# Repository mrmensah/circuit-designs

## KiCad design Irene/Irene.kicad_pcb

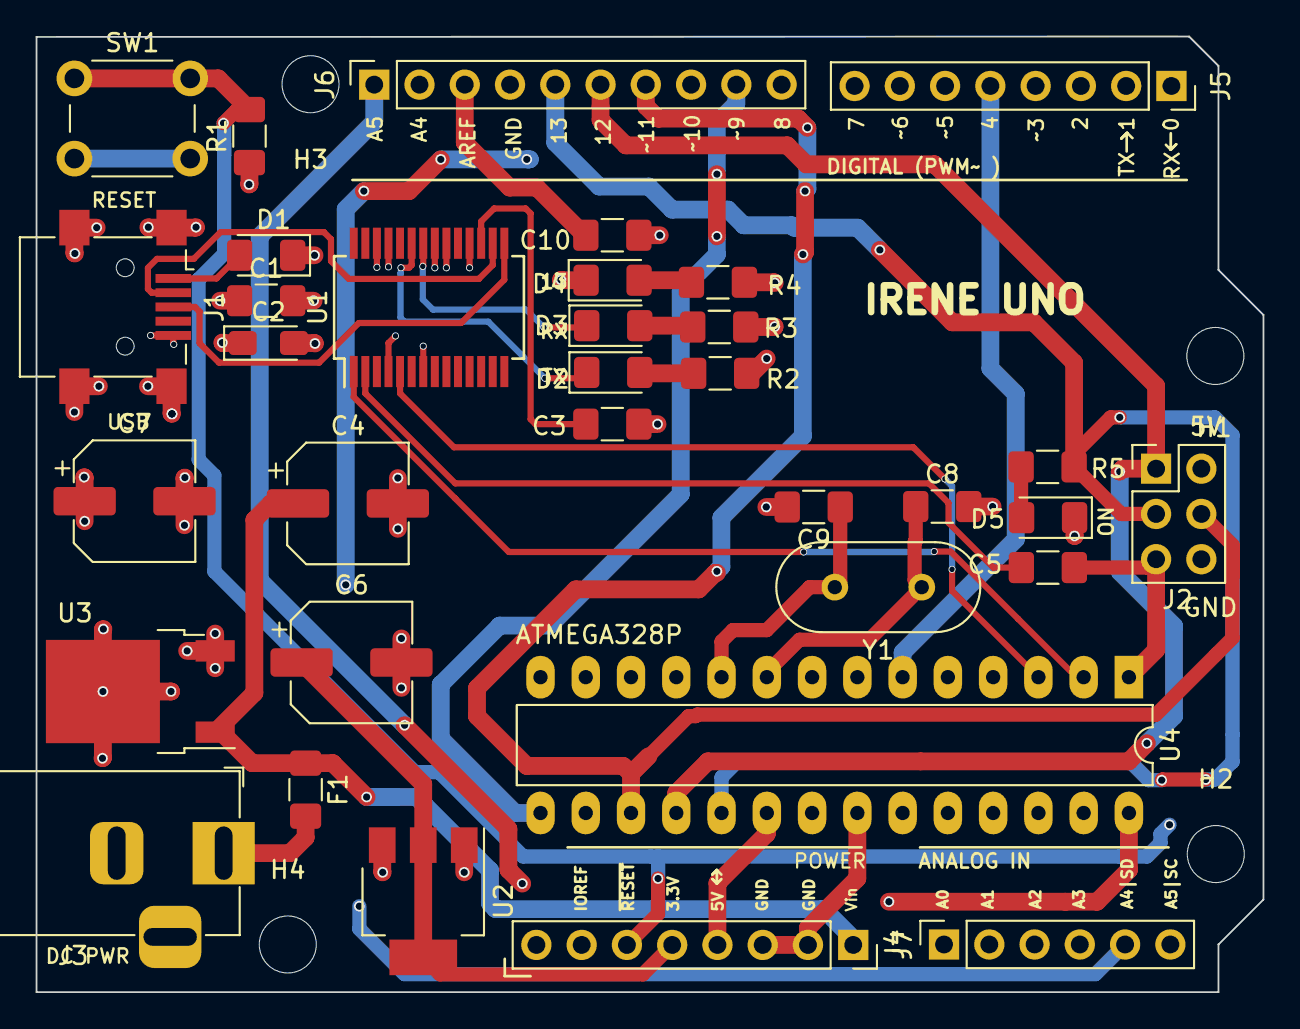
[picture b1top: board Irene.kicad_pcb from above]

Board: 4 copper layers, 68.8 x 53.6 mm, 38 parts (0 on the bottom side), 40 nets.

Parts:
C1, C3, C5, C10: 100nF; C_1206_3216Metric_Pad1.42x1.75mm_HandSolder
C2: 4.7uF; CP_EIA-3216-10_Kemet-I_Pad1.58x1.35mm_HandSolder
C4: 480uF; CP_Elec_6.3x5.4
C6, C7: 100uF; CP_Elec_6.3x5.4
C8, C9: 22pF; C_1206_3216Metric_Pad1.42x1.75mm_HandSolder
D1: D_Schottky; D_1206_3216Metric_Pad1.42x1.75mm_HandSolder
D2: TX LED; LED_1206_3216Metric_Pad1.42x1.75mm_HandSolder
D3: RX LED; LED_1206_3216Metric_Pad1.42x1.75mm_HandSolder
D4: RED; LED_1206_3216Metric_Pad1.42x1.75mm_HandSolder
D5: LED; LED_1206_3216Metric_Pad1.42x1.75mm_HandSolder
F1: 1A; Fuse_1206_3216Metric_Pad1.42x1.75mm_HandSolder
H1: H1; MountingHole_3.2mm_M3
H2: H2; MountingHole_3.2mm_M3
H3: H3; MountingHole_3.2mm_M3
H4: H4; MountingHole_3.2mm_M3
J1: USB_B_Mini; USB_Mini-B_Lumberg_2486_01_Horizontal
J2: AVR-ISP-6; PinHeader_2x03_P2.54mm_Vertical
J3: Barrel_Jack_Switch; BarrelJack_Horizontal
J4: ANALOG PORTS; PinSocket_1x06_P2.54mm_Vertical
J5: D0 - D7; PinSocket_1x08_P2.54mm_Vertical
J6: D8-D13; PinSocket_1x10_P2.54mm_Vertical
J7: POWER PORT; PinSocket_1x08_P2.54mm_Vertical
R1: R; R_1206_3216Metric_Pad1.42x1.75mm_HandSolder
R2, R3: 1K; R_1206_3216Metric_Pad1.42x1.75mm_HandSolder
R4: 10K; R_1206_3216Metric_Pad1.42x1.75mm_HandSolder
R5: R_Small; R_1206_3216Metric_Pad1.42x1.75mm_HandSolder
SW1: SW_Push_Dual; SW_PUSH_6mm_H5mm
U1: FT232RL; SSOP-28_5.3x10.2mm_P0.65mm
U2: AMS1117-3.3; SOT-223-3_TabPin2
U3: LM7805; TO-252-2
U4: ATmega328_DIP; DIP-28_W7.62mm_LongPads
Y1: 16MHz; Crystal_HC49-4H_Vertical

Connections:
+3V3: C6.1, J7.5, U2.2
+5V: C1.1, C2.1, C7.1, D1.1, J2.2, J7.4, J7.7, R1.1, R2.1, R3.1, R4.2, U1.4, U1.20, U2.3, U3.3, U4.7, U4.20
/A0: J4.1, U4.23
/A1: J4.2, U4.24
/A2: J4.3, U4.25
/A3: J4.4, U4.26
/A4: J4.5, J6.2, U4.27
/A5: J4.6, J6.1, U4.28
/AREF: C10.1, J6.3, U4.21
/D2: J5.3, U4.4
/D3: J5.4, U4.5
/D4: J5.5, U4.6
/D5: J5.6, U4.11
/D6: J5.7, U4.12
/D7: J5.8, U4.13
/D8: J6.10, U4.14
/D9: J6.9, U4.15
/D10: J6.8, U4.16
/D11: J2.4, J6.7, U4.17
/D12: J2.1, J6.6, U4.18
/D13: J2.3, J6.5, R5.1, U4.19
/RST: C5.1, J2.5, J7.6, R1.2, SW1.1, U4.1
/RX: J5.2, U1.5, U4.3
/TX: J5.1, U1.1, U4.2
GND: C1.2, C2.2, C3.1, C4.2, C6.2, C7.2, C8.2, C9.2, C10.2, D4.1, D5.1, J1.5, J1.6, J2.6, J3.2, J3.3, J6.4, J7.2, J7.3, SW1.2, U1.7, U1.18, U1.21, U1.25, U1.26, U2.1, U3.2, U4.8, U4.22
unnamed: C3.2, U1.17
unnamed: C5.2, U1.2
unnamed: C8.1, U4.9, Y1.1
unnamed: C9.1, U4.10, Y1.2
unnamed: D1.2, J1.1
unnamed: D2.1, U1.23
unnamed: D2.2, R2.2
unnamed: D3.1, U1.22
unnamed: D3.2, R3.2
unnamed: D4.2, R4.1
unnamed: D5.2, R5.2
unnamed: F1.2, J3.1
unnamed: J1.2, U1.16
unnamed: J1.3, U1.15
VCC: C4.1, F1.1, J7.1, U3.1

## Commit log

2021-02-24 custom arduino UNO board design
